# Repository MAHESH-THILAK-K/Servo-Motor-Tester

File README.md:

# Servo Motor Tester

**A compact 555 timer-based servo tester with adjustable pulse width control for hobby servo testing and calibration.**

## 🔧 Project Overview
A standalone servo tester that generates standard hobby servo PWM signals (50 Hz, 1-2 ms pulses) using an NE555 timer IC configured as an astable multivibrator. A 100kΩ potentiometer provides smooth position control from minimum to maximum servo travel.

**Key goals of this design:**
- Simple analog PWM generation (no microcontroller required)
- Standard 3-pin servo output interface
- Compact, hand-solderable 2-layer PCB
- Visual power/activity indication
- Precise pulse width control via potentiometer

## 📌 Key Features

**Power Input**
- 6V DC via 2-pin header (J1)

**Servo Output** 
- Standard 3-pin header (J2) - VCC/GND/SIG
- Compatible with all hobby servos

**Pulse Control**
- 100kΩ potentiometer (RV1) for 1-2ms pulse width
- Real-time servo position adjustment

**Timing Network**
- R2 (3.3MΩ), R3 (56kΩ), D2 (1N4148)
- C1 (22nF) timing capacitor
- Diode-separated charge/discharge paths

**Status Indication**
- Power LED (D1) with 1kΩ current limiting

## 📂 Repository Structure

```
SERVO-MOTOR-TESTER/
│
├── README.md              # Project documentation
├── LICENSE                # CC-BY-SA-4.0 license
├── Hardware/              # KiCad source files
│   ├── Servo-Motor-Tester.kicad_pro
│   ├── Servo-Motor-Tester.kicad_sch
│   └── Servo-Motor-Tester.kicad_pcb
├── Gerber/                # Manufacturing files
├── 3D MODELS/             # STEP files
├── BOM FILES/             # Bill of materials
└── Images/                # PCB renders & schematics
```

## 🛠️ Hardware Overview

**Core Components**

U1: NE555 Timer (DIP-8) - PWM generation
RV1: 100kΩ Potentiometer - Pulse width control  
C1: 22nF - Timing capacitor
R1: 1kΩ - LED current limit
R2: 3.3MΩ, R3: 56kΩ - Timing resistors
D1: LED - Power indicator
D2: 1N4148 - Charge/discharge diode

**Connectors**

J1 (2-pin): VCC (6V), GND - Power input
J2 (3-pin): GND, VCC, SIG - Servo output

**Mechanical**
- Four M2 mounting holes
- Compact ~35×25mm PCB
- Clear silkscreen labeling

## 🔌 Connections

Power Input (J1):
Pin 1 ── VCC (6V DC)
Pin 2 ── GND

Servo Output (J2):  
Pin 1 ── GND
Pin 2 ── VCC (6V)
Pin 3 ── SIG (PWM)

## 🏭 Manufacturing

The Gerber files include:
- Top/Bottom copper layers
- Solder mask & silkscreen
- Drill files & board outline
- Ready for JLCPCB, PCBWay, or any PCB fab

**PCB Specs:**
- 2-layer, 1.6mm thickness
- Hand-solderable SMD + THT mix

## 🚀 Build Instructions

1. Solder SMD resistors (R1, R2, R3 - 0805)
2. Install 555 timer (DIP-8 socket recommended)  
3. Solder THT components (C1, D1, D2, RV1)
4. Mount headers (J1, J2)
5. Power with 6V DC supply
6. Connect servo to J2
7. Adjust RV1 for servo position control

## 📄 Firmware
**No firmware required** - Pure analog 555 timer design

## 📸Diagrams
Board renders, schematics, and assembly photos available in:
- `Hardware/` - KiCad source files
- `Images/` - Visual documentation

## 📜 License
**CC-BY-SA-4.0** - Free to use, modify, and share with attribution.

## 🙌 Contributions
Contributions, improvements, and documentation updates welcome. Open issues or pull requests.

## 📧 Contact
For questions or collaboration, open an Issue or contact **Thilak**.

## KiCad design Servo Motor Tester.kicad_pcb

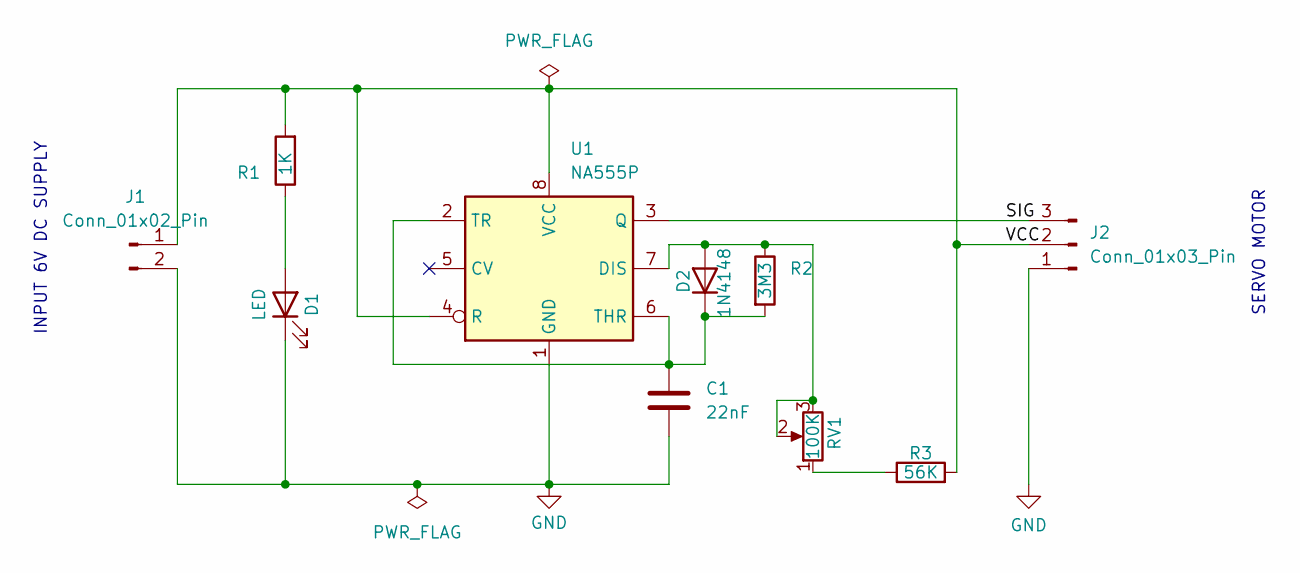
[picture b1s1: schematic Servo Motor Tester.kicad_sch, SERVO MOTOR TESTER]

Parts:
C1: 22nF; C_Disc_D4.3mm_W1.9mm_P5.00mm
D1: LED; LED_D3.0mm
D2: 1N4148; D_DO-35_SOD27_P7.62mm_Horizontal
J1: Conn_01x02_Pin; PinHeader_1x02_P2.54mm_Horizontal
J2: Conn_01x03_Pin; PinHeader_1x03_P2.54mm_Horizontal
R1: 1K; R_0805_2012Metric_Pad1.20x1.40mm_HandSolder
R2: 3M3; R_0805_2012Metric_Pad1.20x1.40mm_HandSolder
R3: 56K; R_0805_2012Metric_Pad1.20x1.40mm_HandSolder
RV1: 100K; Potentiometer_Alps_RK163_Single_Horizontal
U1: NA555P; DIP-8_W7.62mm

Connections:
/SIG: J2.3, U1.3 (Q)
/VCC: J1.1, J2.2, R1.2, R3.2, U1.4 (R), U1.8 (VCC)
GND: C1.2, D1.1 (K), J1.2, J2.1, U1.1 (GND)
unnamed: D1.2 (A), R1.1
unnamed: D2.2 (A), R2.1, RV1.2, RV1.3, U1.7 (DIS)
unnamed: C1.1, D2.1 (K), R2.2, U1.2 (TR), U1.6 (THR)
unnamed: R3.1, RV1.1

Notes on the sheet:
INPUT 6V DC SUPPLY
SERVO MOTOR

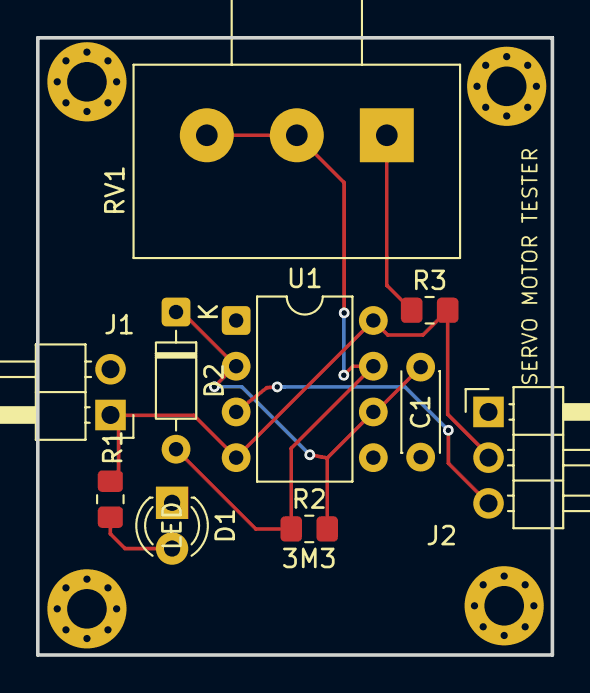
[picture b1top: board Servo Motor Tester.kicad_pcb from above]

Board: 2 copper layers, 28.6 x 34.3 mm, 10 parts (0 on the bottom side), 7 nets.
